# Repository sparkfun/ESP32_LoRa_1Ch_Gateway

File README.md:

SparkFun LoRa Gateway 1-Channel
========================================

[*SparkFun LoRa Gateway 1-Channel (15006)*](https://www.sparkfun.com/products/15006)

A programmable microcontroller featuring both WiFi and Bluetooth radios -- with an RFM95W LoRa transceiver to create a single-channel LoRa gateway. It's a perfect, low-cost tool for monitoring a dozen-or-so LoRa devices, and relaying their messages up to the cloud.

Repository Contents
-------------------

* **/Documentation** - Data sheets, additional product information
* **/Firmware** - Example code 
* **/Hardware** - Eagle design files (.brd, .sch)

Documentation
--------------
* **[Library](https://github.com/sparkfun/ESP32_LoRa_1Ch_Gateway)** - Arduino library for the SparkFun LoRa Gateway 1-Channel.
* **[Hookup Guide](https://learn.sparkfun.com/tutorials/sparkfun-lora-gateway-1-channel-hookup-guide)** - Basic hookup guide for the SparkFun LoRa Gateway 1-Channel.
* **[SparkFun Fritzing repo](https://github.com/sparkfun/Fritzing_Parts)** - Fritzing diagrams for SparkFun products.

Product Versions
----------------
* [15006](https://www.sparkfun.com/products/15006) - SparkFun LoRa Gateway 1-Channel

Version History
---------------
* [v10](https://github.com/sparkfun/ESP32_LoRa_1Ch_Gateway/releases/tag/v10) - Initial redboard release

License Information
-------------------

This product is _**open source**_! 

Please review the LICENSE.md file for license information. 

If you have any questions or concerns on licensing, please contact techsupport@sparkfun.com.

Distributed as-is; no warranty is given.

- Your friends at SparkFun.

_<COLLABORATION CREDIT>_

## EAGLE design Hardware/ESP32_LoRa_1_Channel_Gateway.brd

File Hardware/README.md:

SparkFun <PRODUCT NAME> Design Files
=====================================

The .sch and .brd files hare are Eagle CAD schematic and PCB design files from SparkFun Electronics.
A freeware version of Eagle can be found [here](http://www.cadsoftusa.com/download-eagle/freeware/).

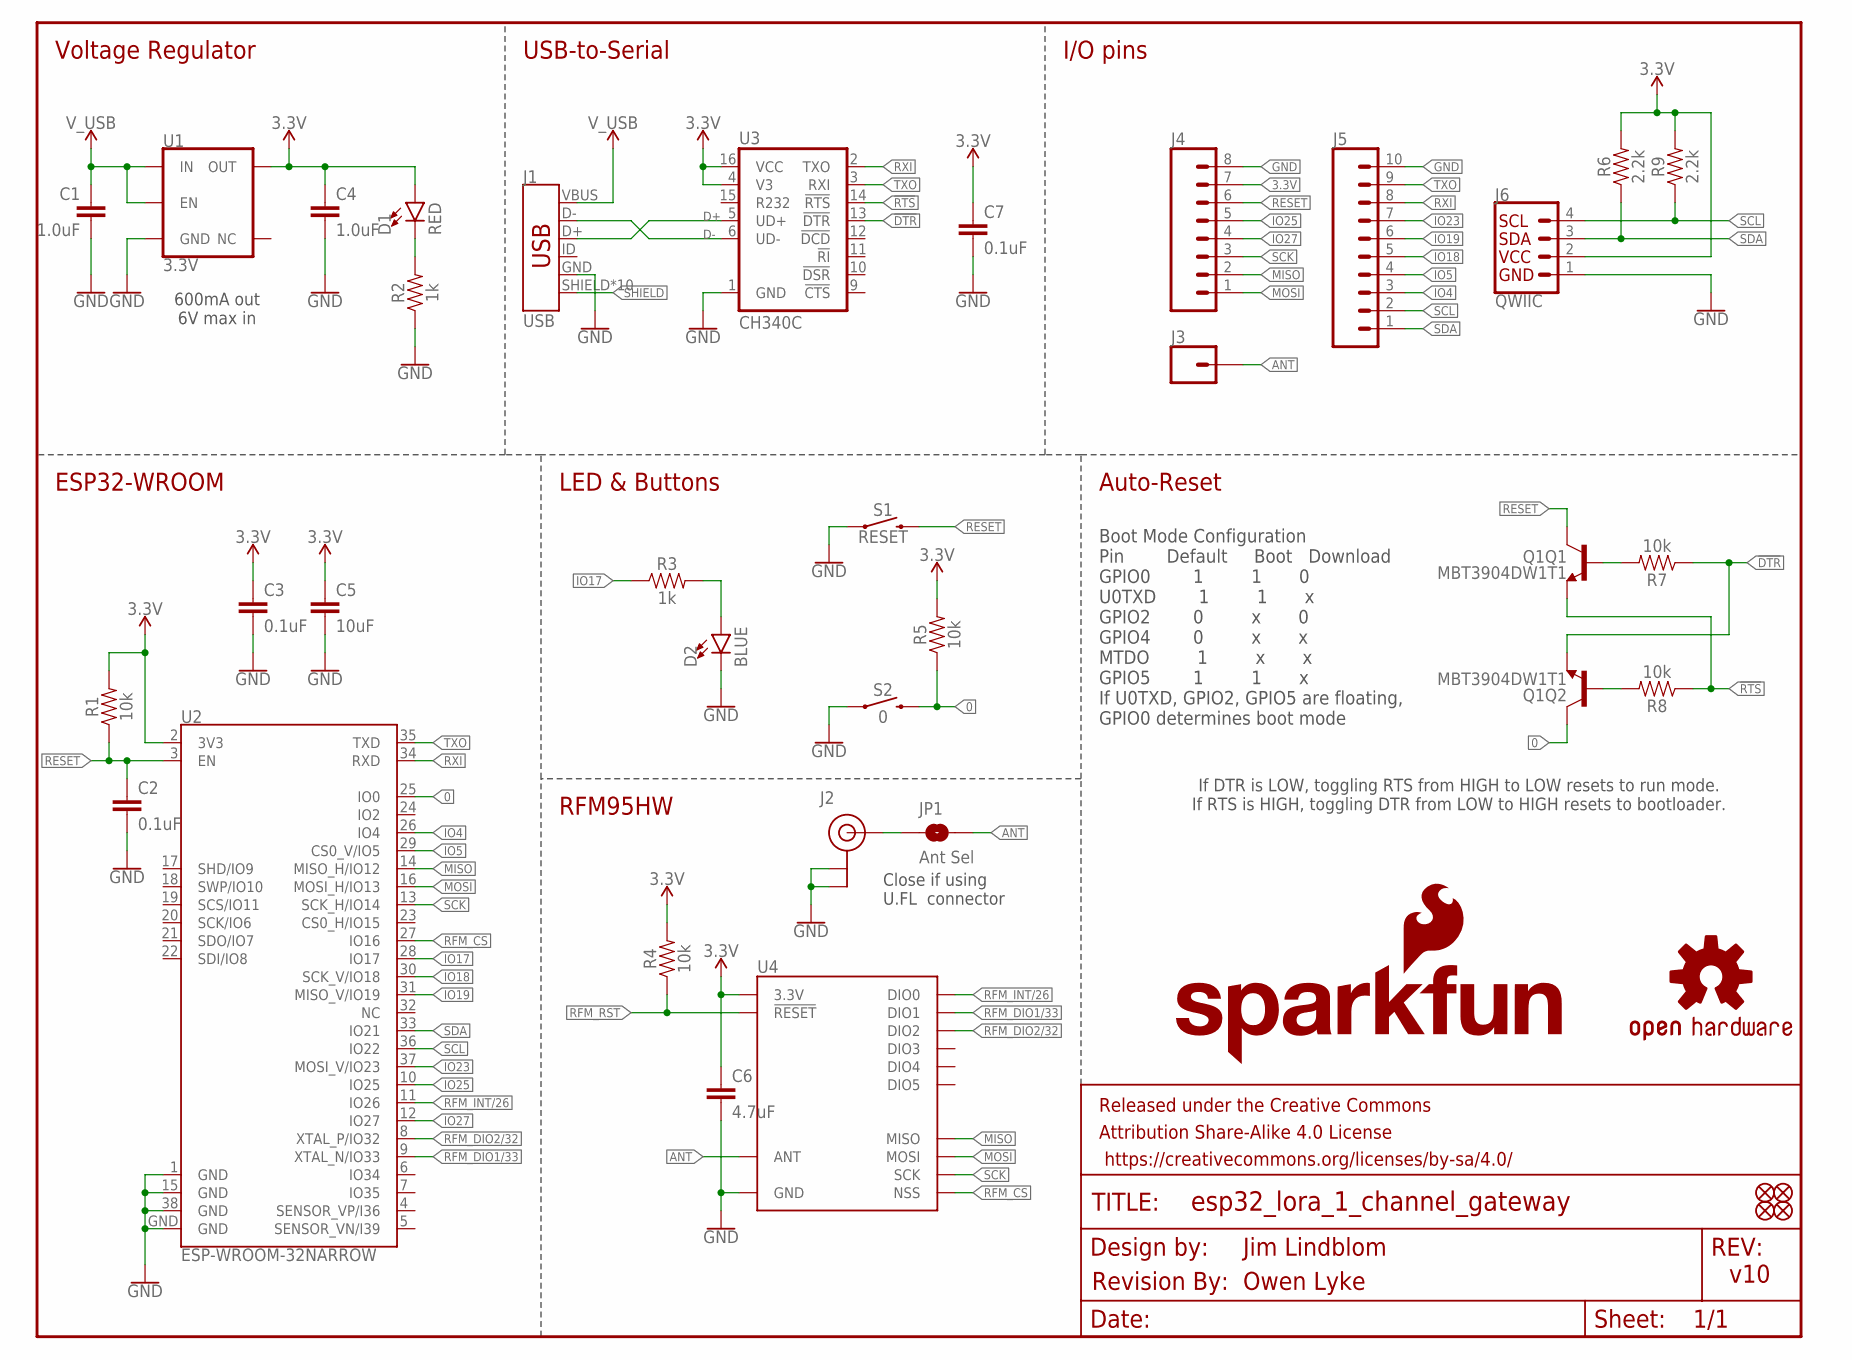
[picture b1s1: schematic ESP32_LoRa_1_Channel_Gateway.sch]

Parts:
C1, C4: 1.0uF; 0603
C2, C3, C7: 0.1uF; 0603
C5: 10uF; 0603
C6: 4.7uF; 0603
D1: RED; LED-0603
D2: BLUE; LED-0603
FD1, FD2, FD3, FD4: FIDUCIAL1X2; FIDUCIAL-1X2
FRAME1: FRAME-LETTER; CREATIVE_COMMONS
J1: USB; USB-MICROB-PTH-MILL
J2: U.FL
J3: CONN_01PTH_NO_SILK_YES_STOP; 1X01_NO_SILK
J4: CONN_08NO_SILK_FEMALE_PTH; 1X08_NO_SILK
J5: CONN_10NO_SILK_PTH_FEMALE; 1X10_NO_SILK
J6: QWIIC; 1X04_1MM_RA
JP1: Ant Sel; SMT-JUMPER_2_NO_NO-SILK
LOGO1: REVISION
LOGO2: SFE_LOGO_NAME_FLAME.1_INCH; SFE_LOGO_NAME_FLAME_.1
LOGO3: OSHW-LOGOS; OSHW-LOGO-S
Q1: MBT3904DW1T1; SC70-6
R1, R4, R5, R7, R8: 10k; 0603
R2, R3: 1k; 0603
R6, R9: 2.2k; 0603
S1: RESET; TACTILE_SWITCH_SMD_4.6X2.8MM
S2: 0; TACTILE_SWITCH_SMD_4.6X2.8MM
U1: 3.3V; SOT23-5
U2: ESP-WROOM-32NARROW; ESP-WROOM-32-NARROW
U3: CH340C; SO016
U4: RFM95W; RFM95/96/97/98W

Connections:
0: Q1.6 (C), R5.1, S2.3 (2), S2.4 (2), U2.25 (IO0)
3.3V: C3.1, C4.1, C5.1, C6.1, C7.1, D1.A, J4.7, J6.2, R1.2, R4.2, R5.2, R6.2, R9.2, U1.5 (OUT), U2.2 (3V3), U3.4 (V3), U3.16 (VCC), U4.3.3V
!DTR: Q1.1 (E), R7.1, U3.13 (!DTR)
!RTS: Q1.4 (E), R8.1, U3.14 (!RTS)
ANT: J3.1, JP1.2, U4.ANT
D+: J1.D+, U3.5 (UD+)
D-: J1.D-, U3.6 (UD-)
GND: C1.2, C2.2, C3.2, C4.2, C5.2, C6.2, C7.2, D2.C, J1.GND, J2.1 (GND), J2.2 (GND), J4.8, J5.10, J6.1, R2.1, S1.1, S1.2 (1), S2.1, S2.2 (1), U1.2 (GND), U2.1 (GND), U2.15 (GND), U2.38 (GND), U2.GND, U3.1 (GND), U4.GND@1 (GND), U4.GND@2 (GND), U4.GND@3 (GND)
IO4: J5.3, U2.26 (IO4)
IO5: J5.4, U2.29 (CS0_V/IO5)
IO17: R3.1, U2.28 (IO17)
IO18: J5.5, U2.30 (SCK_V/IO18)
IO19: J5.6, U2.31 (MISO_V/IO19)
IO23: J5.7, U2.37 (MOSI_V/IO23)
IO25: J4.5, U2.10 (IO25)
IO27: J4.4, U2.12 (IO27)
MISO: J4.2, U2.14 (MISO_H/IO12), U4.MISO
MOSI: J4.1, U2.16 (MOSI_H/IO13), U4.MOSI
unnamed: D1.C, R2.2
unnamed: D2.A, R3.2
unnamed: J2.FEED (SIGNAL), JP1.1
unnamed: Q1.5 (B), R7.2
unnamed: Q1.2 (B), R8.2
RESET: C2.1, J4.6, Q1.3 (C), R1.1, S1.3 (2), S1.4 (2), U2.3 (EN)
RFM_CS: U2.27 (IO16), U4.NSS
RFM_DIO1/33: U2.9 (XTAL_N/IO33), U4.DIO1
RFM_DIO2/32: U2.8 (XTAL_P/IO32), U4.DIO2
RFM_INT/26: U2.11 (IO26), U4.DIO0
RFM_RST: R4.1, U4.!RESET
RXI: J5.8, U2.34 (RXD), U3.2 (TXO)
SCK: J4.3, U2.13 (SCK_H/IO14), U4.SCK
SCL: J5.2, J6.4, R9.1, U2.36 (IO22)
SDA: J5.1, J6.3, R6.1, U2.33 (IO21)
SHIELD: J1.SHIELD, J1.SHIELD2 (SHIELD), J1.SHIELD3 (SHIELD), J1.SHIELD4 (SHIELD), J1.SHIELD5 (SHIELD), J1.SHIELD6 (SHIELD), J1.SHIELD7 (SHIELD), J1.SHIELD8 (SHIELD), J1.SHIELD9 (SHIELD), J1.SHIELD10 (SHIELD)
TXO: J5.9, U2.35 (TXD), U3.3 (RXI)
V_USB: C1.1, J1.VBUS, U1.1 (IN), U1.3 (EN)

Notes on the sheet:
Boot Mode Configuration Pin Default Boot Download GPIO0 1 1 0 U0TXD 1 1 x GPIO2 0 x 0 GPIO4 0 x x MTDO 1 x x GPIO5 1 1 x If U0TXD, GPIO2, GPIO5 are floating, GPIO0 determines boot mode
If DTR is LOW, toggling RTS from HIGH to LOW resets to run mode. If RTS is HIGH, toggling DTR from LOW to HIGH resets to bootloader.
600mA out 6V max in
Voltage Regulator
USB-to-Serial
I/O pins
ESP32-WROOM
LED & Buttons
Auto-Reset
RFM95HW
Jim Lindblom
v10
Owen Lyke
Close if using U.FL connector

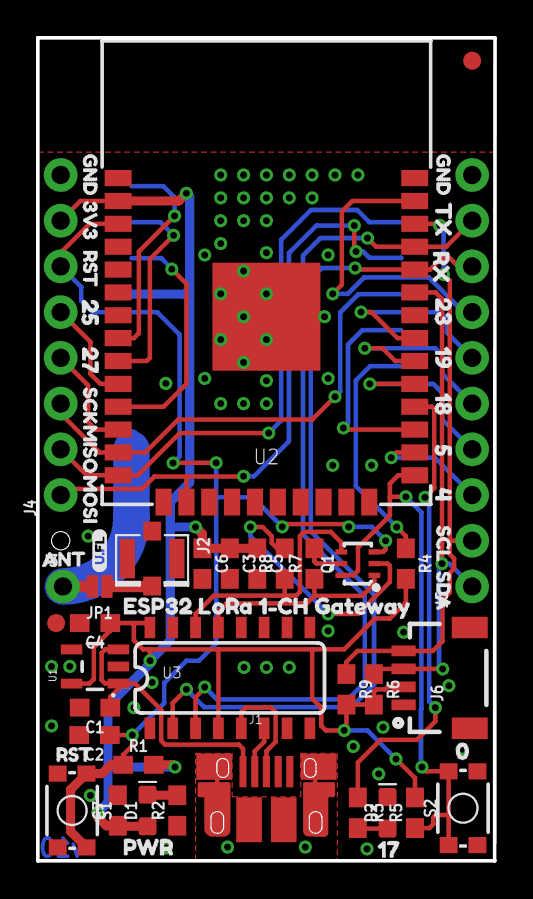
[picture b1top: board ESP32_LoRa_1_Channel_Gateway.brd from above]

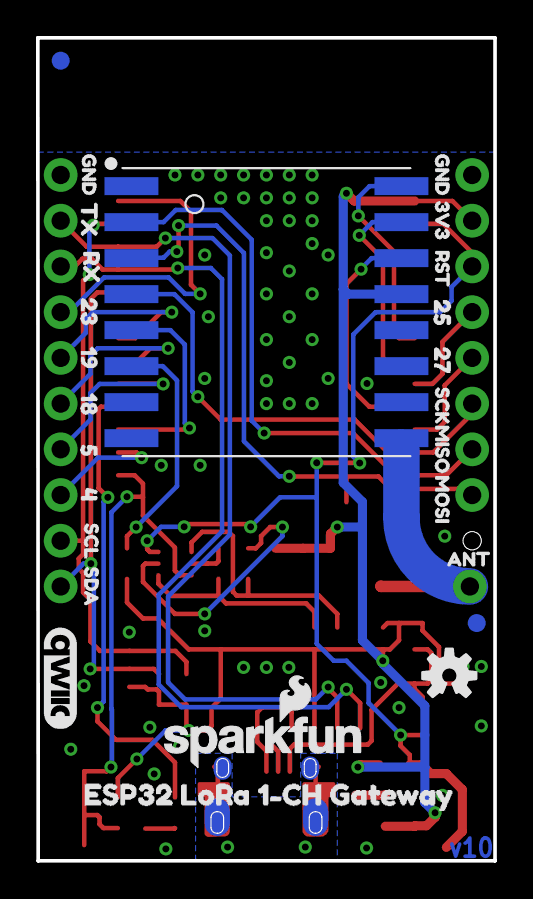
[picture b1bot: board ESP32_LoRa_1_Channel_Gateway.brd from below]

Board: 2 copper layers, 25.4 x 45.7 mm, 86 parts (26 on the bottom side), 36 nets.

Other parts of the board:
U$1, U$10, U$26, U$37: GND0
U$2, U$38: 3V31
U$3, U$20, U$39: RST2
U$4, U$40: 2517
U$5, U$41: 279
U$6, U$42: SCK3
U$7, U$43: MISO4
U$8, U$44: MOSI5
U$9, U$36: ANT6
U$11, U$27: TX16
U$12, U$28: RX15
U$13, U$29: 2314
U$14, U$30: 1912
U$15, U$31: 1811
U$16, U$32: 513
U$17, U$33: 410
U$18, U$34: SCL8
U$19, U$35: SDA7
U$21: 020
U$22: PWR19
U$23: 1722
U$24: U#FL0
U$25: ESP32_LORA_1#CH_GATEWAY21
U$45: ESP32_LORA_1#CH_GATEWAY23
U$46: QWIIC_COPYRIGHT_SMALL

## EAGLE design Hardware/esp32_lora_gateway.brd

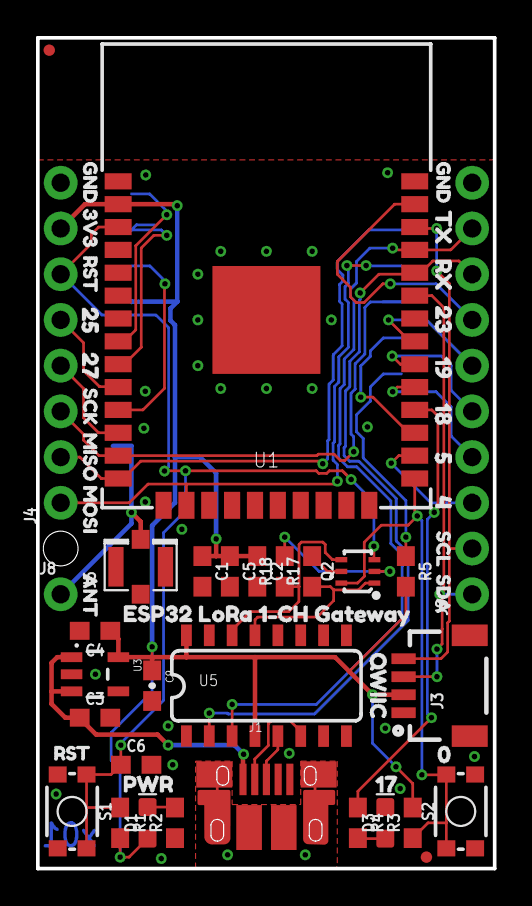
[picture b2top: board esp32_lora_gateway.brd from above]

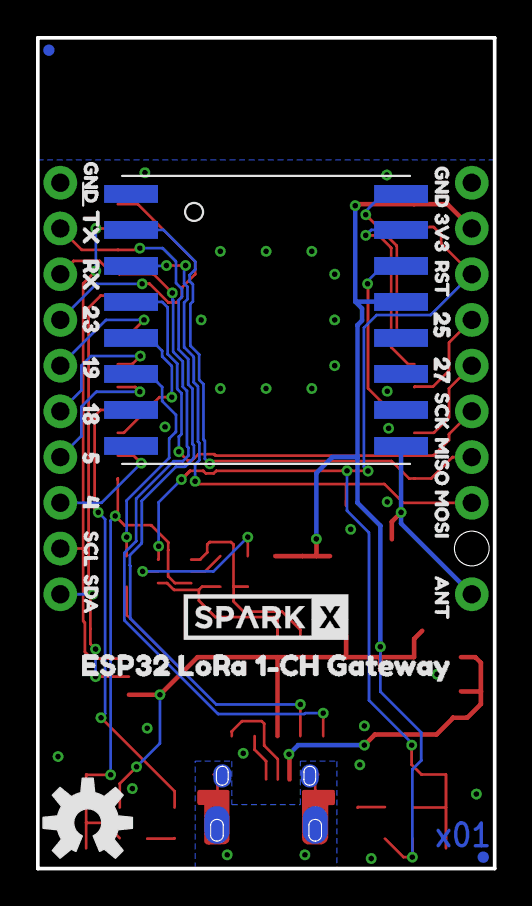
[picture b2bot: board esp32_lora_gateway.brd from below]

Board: 2 copper layers, 25.4 x 46.2 mm, 81 parts (25 on the bottom side), 35 nets.

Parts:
C1: 4.7uF; 0603
C2: 10uF; 0603
C3, C4: 1.0uF; 0603
C5, C6: 0.1uF; 0603
C9: 0.1uF; 0603-CAP
D1: RED; LED-0603
D3: GREEN; LED-0603
FD1, FD2, FD3, FD4: FIDUCIALUFIDUCIAL; FIDUCIAL-MICRO
FRAME1: FRAME-LETTER; CREATIVE_COMMONS
J1: USB; USB-MICROB-PTH-MILL
J3: QWIIC; 1X04_1MM_RA
J4: 1X08_NO_SILK
J5: U.FL
J8: 1X01_NO_SILK
J9: 1X10_NO_SILK
LOGO1: SPARKX-LOGO4; SPARKX-MEDIUM
LOGO2: OSHW-LOGOM; OSHW-LOGO-M
Q2: MBT3904DW1T1; SC70-6
R1, R3, R5, R17, R18: 10k; 0603
R2, R4: 1k; 0603
S1: RESET; TACTILE_SWITCH_SMD_4.6X2.8MM
S2: 0; TACTILE_SWITCH_SMD_4.6X2.8MM
U1: ESP-WROOM-32NARROW; ESP-WROOM-32-NARROW
U2: RFM96W; RFM95/96/97/98W
U3: 3.3V; SOT23-5
U5: CH340C; SO016
U$1, U$10, U$26, U$37: GND0
U$2, U$38: 3V31
U$3, U$20, U$39: RST2
U$4, U$40: 2517
U$5, U$41: 279
U$6, U$42: SCK3
U$7, U$43: MISO4
U$8, U$44: MOSI5
U$9, U$36: ANT6
U$11, U$27: TX16
U$12, U$28: RX15
U$13, U$29: 2314
U$14, U$30: 1912
U$15, U$31: 1811
U$16, U$32: 513
U$17, U$33: 410
U$18, U$34: SCL8
U$19, U$35: SDA7
U$21: 020
U$22: PWR19
U$23: 1722
U$24: QWIIC18
U$25: ESP32_LORA_1#CH_GATEWAY21
U$45: ESP32_LORA_1#CH_GATEWAY23

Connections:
0: Q2.6, R3.1, S2.3, S2.4, U1.25
3.3V: C1.1, C2.1, C4.1, C5.1, C9.1, D1.A, J3.2, J4.7, R1.2, R3.2, R5.2, U1.2, U2.3.3V, U3.5, U5.4, U5.16
!DTR: Q2.1, R17.1, U5.13
!RTS: Q2.4, R18.1, U5.14
ANT: J5.FEED, J8.1, U2.ANT
D+: J1.D+, U5.5
D-: J1.D-, U5.6
GND: C1.2, C2.2, C3.2, C4.2, C5.2, C6.2, C9.2, D3.C, J1.GND, J3.1, J4.8, J5.1, J5.2, J9.10, R2.1, S1.1, S1.2, S2.1, S2.2, U1.1, U1.15, U1.38, U1.GND, U2.GND@1, U2.GND@2, U2.GND@3, U3.2, U5.1
IO4: J9.3, U1.26
IO5: J9.4, U1.29
IO17: R4.1, U1.28
IO18: J9.5, U1.30
IO19: J9.6, U1.31
IO23: J9.7, U1.37
IO25: J4.5, U1.10
IO27: J4.4, U1.12
MISO: J4.2, U1.14, U2.MISO
MOSI: J4.1, U1.16, U2.MOSI
unnamed: D1.C, R2.2
unnamed: D3.A, R4.2
unnamed: Q2.5, R17.2
unnamed: Q2.2, R18.2
RESET: C6.1, J4.6, Q2.3, R1.1, S1.3, S1.4, U1.3
RFM_CS: U1.27, U2.NSS
RFM_DIO1/33: U1.9, U2.DIO1
RFM_DIO2/32: U1.8, U2.DIO2
RFM_INT/26: U1.11, U2.DIO0
RFM_RST: R5.1, U2.!RESET
RXI: J9.8, U1.34, U5.2
SCK: J4.3, U1.13, U2.SCK
SCL: J3.4, J9.2, U1.36
SDA: J3.3, J9.1, U1.33
SHIELD: J1.SHIELD, J1.SHIELD2, J1.SHIELD3, J1.SHIELD4, J1.SHIELD5, J1.SHIELD6, J1.SHIELD7, J1.SHIELD8, J1.SHIELD9, J1.SHIELD10
TXO: J9.9, U1.35, U5.3
V_USB: C3.1, J1.VBUS, U3.1, U3.3

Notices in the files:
parts and their libraries:
SparkFun-Capacitors: Licensing: Creative Commons ShareAlike 4.0 International - https://creativecommons.org/licenses/by-sa/4.0
SparkFun-Aesthetics: Released under the Creative Commons Attribution Share-Alike 4.0 License
SparkFun-Aesthetics: https://creativecommons.org/licenses/by-sa/4.0
